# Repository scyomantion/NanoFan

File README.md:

# NanoFan

A custom fan controller for HP D2600 based on Arduino Nano

It is a header for Arduino Nano. You connect the fans with the header and the header with the old fan plugs so that the Arduino acts like a man in the middle. 

The original fans could be controlled by a pwm signal and there is a fake rpm signal sent to the original controller.

## Disclaimer

I'm not responsible for anything that happens by building or using this project

## Images

## BOM

You need following per fan controller:

- 1x Arduino Nano

- 2x JUMPER 04KR-6S-P - 04KR-6S-P 2" (PN: A04KR04KR26E51B)

- 4x B4B-PH-K-S(LF)(SN)

- 1x PCB from this project

## Impressum

[Impressum](https://banjobyte.com/impressum.html)

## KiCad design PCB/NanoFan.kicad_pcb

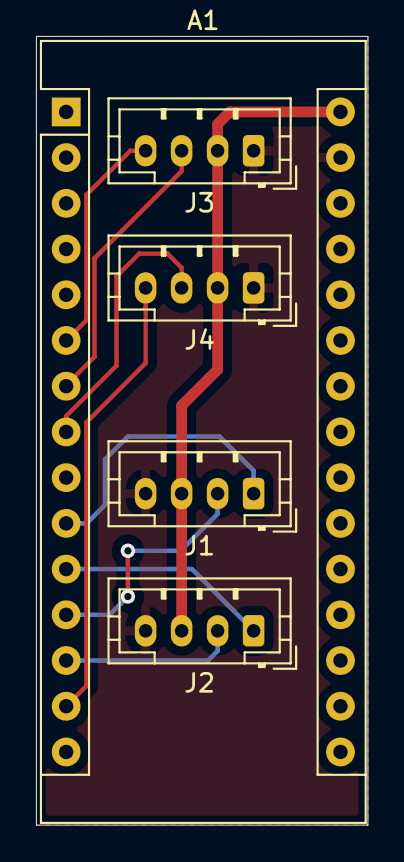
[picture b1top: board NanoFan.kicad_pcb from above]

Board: 2 copper layers, 18.4 x 43.8 mm, 5 parts (0 on the bottom side), 10 nets.

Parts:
A1: Arduino_Nano_v3.x; Arduino_Nano
J1, J2, J3, J4: Conn_01x04_Male; JST_PH_B4B-PH-K_1x04_P2.00mm_Vertical

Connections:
+12V: A1.30, J1.3, J2.3, J3.2, J4.2
ControlC1: A1.10, J1.1
ControlC2: A1.11, J2.1
ControlF1: A1.6, J3.4
ControlF2: A1.14, J4.4
GND: A1.4, A1.29, J1.4, J2.4, J3.1, J4.1
SenseC1: A1.12, J1.2
SenseC2: A1.13, J2.2
SenseF1: A1.7, J3.3
SenseF2: A1.8, J4.3

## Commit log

2020-08-29 add gerber files
2020-09-10 Update README.md
    correct BOM
2020-09-14 Add Impressum to Readme
